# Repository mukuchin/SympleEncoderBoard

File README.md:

SympleEncoderBoard

エンコーダー用基板

神山先輩の回路をEagleで改良したもの

### dipスイッチについて

- 1～6番はエンコーダの回転向きの定義を切り替えるために使う。1～4番はエンコーダの1～4番の向きが切り替わる。5はX,6はY。

- 7は速度を出力するのか、積分したあとの位置を出力するかを切り替える。

- 8は2枚目のボードをつないだときに識別できるようにボード番号を切り替えるためのもの。

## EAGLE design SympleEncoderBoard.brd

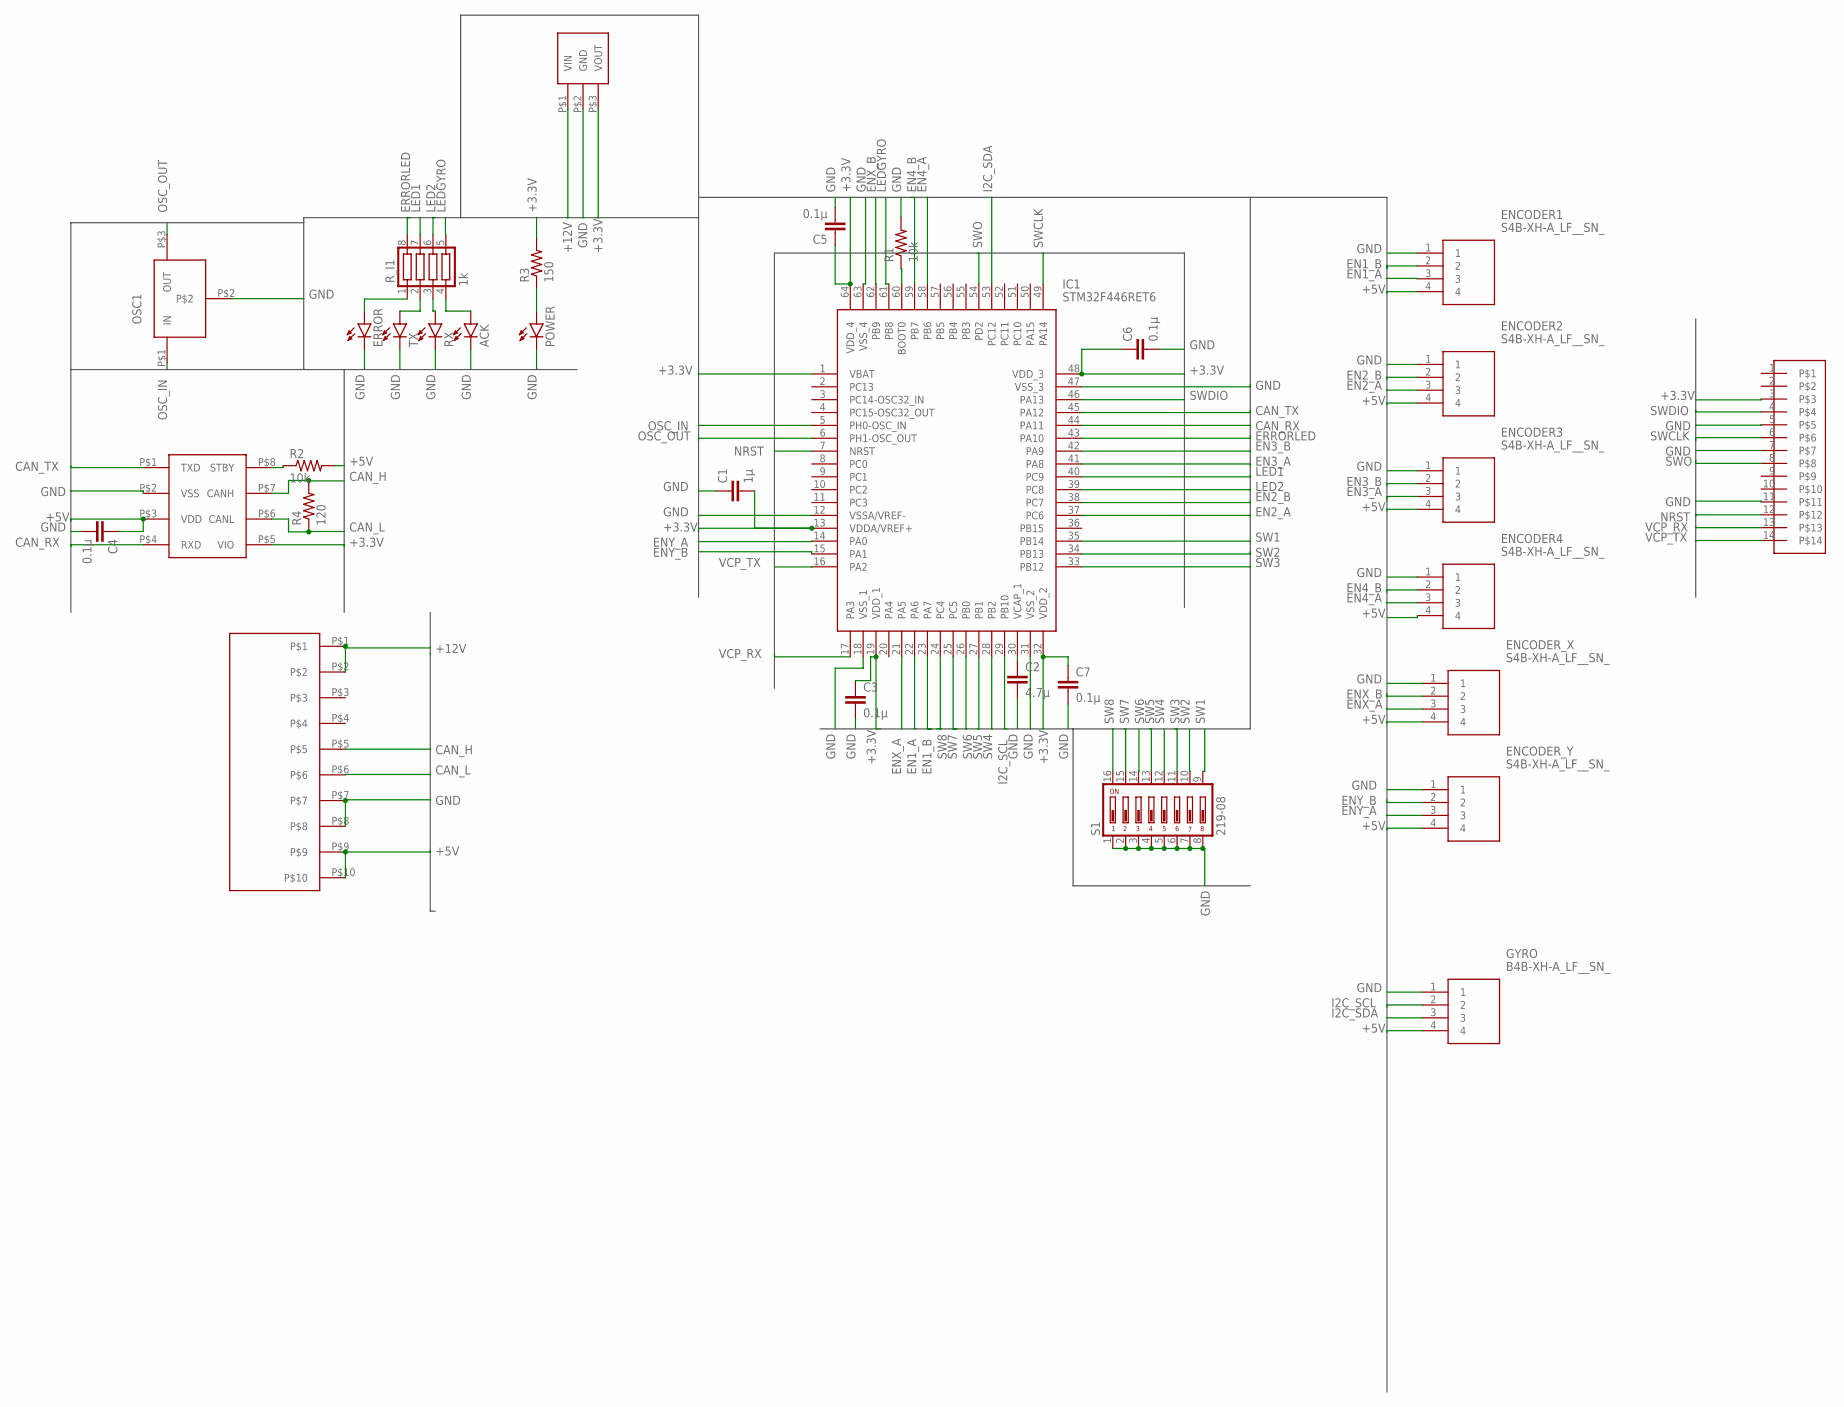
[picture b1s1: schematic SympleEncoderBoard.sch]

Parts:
ACK: LEDCHIPLED_0603; CHIPLED_0603
C1: 1μ; C1608
C2: 4.7μ; C0603
C3, C5, C6, C7: 0.1μ; C0603
C4: 0.1μ; C1608
ENCODER1, ENCODER2, ENCODER3, ENCODER4: S4B-XH-A_LF__SN_; SHDRRA4W64P0X250_1X4_1240X1150
ENCODER_X: S4B-XH-A_LF__SN_; SHDRRA4W64P0X250_1X4_1240X1150
ENCODER_Y: S4B-XH-A_LF__SN_; SHDRRA4W64P0X250_1X4_1240X1150
ERROR: LEDCHIPLED_0603; CHIPLED_0603
GYRO: B4B-XH-A_LF__SN_; SHDR4W64P0X250_1X4_1240X575X70
IC1: STM32F446RET6; QFP50P1200X1200X160-64N
OSC1: CSTN#; CSTNE#
POWER: LEDCHIPLED_0603; CHIPLED_0603
R1, R2: 10k; R0603
R3: 150; R0603
R4: 120; R0603
RX: LEDCHIPLED_0603; CHIPLED_0603
R_I1: 1k; 0603X4RESISTOR
S1: 219-08; CTS-219-08
TX: LEDCHIPLED_0603; CHIPLED_0603
U$1: BOX14P; CON_HEDA14P_1.27
U$2: BP5293-33; DC/DC_REGULATOR_3P
U$3: MCP2562MCP2561-SN; SOIC8
U$4: BOX10PBOX10P-L; BOX10P-L

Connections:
+3.3V: C1.2, C3.1, C5.1, C6.1, C7.1, IC1.1 (VBAT), IC1.13 (VDDA/VREF+), IC1.19 (VDD_1), IC1.32 (VDD_2), IC1.48 (VDD_3), IC1.64 (VDD_4), R3.2, U$1.3, U$2.P$3 (VOUT), U$3.P$5 (VIO)
+5V: C4.1, ENCODER1.4, ENCODER2.4, ENCODER3.4, ENCODER4.4, ENCODER_X.4, ENCODER_Y.4, GYRO.4, R2.2, U$3.P$3 (VDD), U$4.P$9, U$4.P$10
+12V: U$2.P$1 (VIN), U$4.P$1, U$4.P$2
CAN_H: R4.2, U$3.P$7 (CANH), U$4.P$5
CAN_L: R4.1, U$3.P$6 (CANL), U$4.P$6
CAN_RX: IC1.44 (PA11), U$3.P$4 (RXD)
CAN_TX: IC1.45 (PA12), U$3.P$1 (TXD)
EN1_A: ENCODER1.3, IC1.22 (PA6)
EN1_B: ENCODER1.2, IC1.23 (PA7)
EN2_A: ENCODER2.3, IC1.37 (PC6)
EN2_B: ENCODER2.2, IC1.38 (PC7)
EN3_A: ENCODER3.3, IC1.41 (PA8)
EN3_B: ENCODER3.2, IC1.42 (PA9)
EN4_A: ENCODER4.3, IC1.58 (PB6)
EN4_B: ENCODER4.2, IC1.59 (PB7)
ENX_A: ENCODER_X.3, IC1.21 (PA5)
ENX_B: ENCODER_X.2, IC1.62 (PB9)
ENY_A: ENCODER_Y.3, IC1.14 (PA0)
ENY_B: ENCODER_Y.2, IC1.15 (PA1)
ERRORLED: IC1.43 (PA10), R_I1.8
GND: ACK.C, C1.1, C2.2, C3.2, C4.2, C5.2, C6.2, C7.2, ENCODER1.1, ENCODER2.1, ENCODER3.1, ENCODER4.1, ENCODER_X.1, ENCODER_Y.1, ERROR.C, GYRO.1, IC1.12 (VSSA/VREF-), IC1.18 (VSS_1), IC1.31 (VSS_2), IC1.47 (VSS_3), IC1.63 (VSS_4), OSC1.P$2, POWER.C, R1.2, RX.C, S1.1, S1.2, S1.3, S1.4, S1.5, S1.6, S1.7, S1.8, TX.C, U$1.5, U$1.7, U$1.11, U$2.P$2 (GND), U$3.P$2 (VSS), U$4.P$7, U$4.P$8
I2C_SCL: GYRO.2, IC1.29 (PB10)
I2C_SDA: GYRO.3, IC1.53 (PC12)
LED1: IC1.40 (PC9), R_I1.7
LED2: IC1.39 (PC8), R_I1.6
LEDGYRO: IC1.61 (PB8), R_I1.5
unnamed: IC1.60 (BOOT0), R1.1
unnamed: C2.1, IC1.30 (VCAP_1)
unnamed: ERROR.A, R_I1.1
unnamed: R_I1.2, TX.A
unnamed: RX.A, R_I1.3
unnamed: ACK.A, R_I1.4
unnamed: R2.1, U$3.P$8 (STBY)
unnamed: POWER.A, R3.1
NRST: IC1.7 (NRST), U$1.12
OSC_IN: IC1.5 (PH0-OSC_IN), OSC1.P$1 (IN)
OSC_OUT: IC1.6 (PH1-OSC_OUT), OSC1.P$3 (OUT)
SW1: IC1.35 (PB14), S1.9
SW2: IC1.34 (PB13), S1.10
SW3: IC1.33 (PB12), S1.11
SW4: IC1.28 (PB2), S1.12
SW5: IC1.27 (PB1), S1.13
SW6: IC1.26 (PB0), S1.14
SW7: IC1.25 (PC5), S1.15
SW8: IC1.24 (PC4), S1.16
SWCLK: IC1.49 (PA14), U$1.6
SWDIO: IC1.46 (PA13), U$1.4
SWO: IC1.54 (PD2), U$1.8
VCP_RX: IC1.17 (PA3), U$1.13
VCP_TX: IC1.16 (PA2), U$1.14

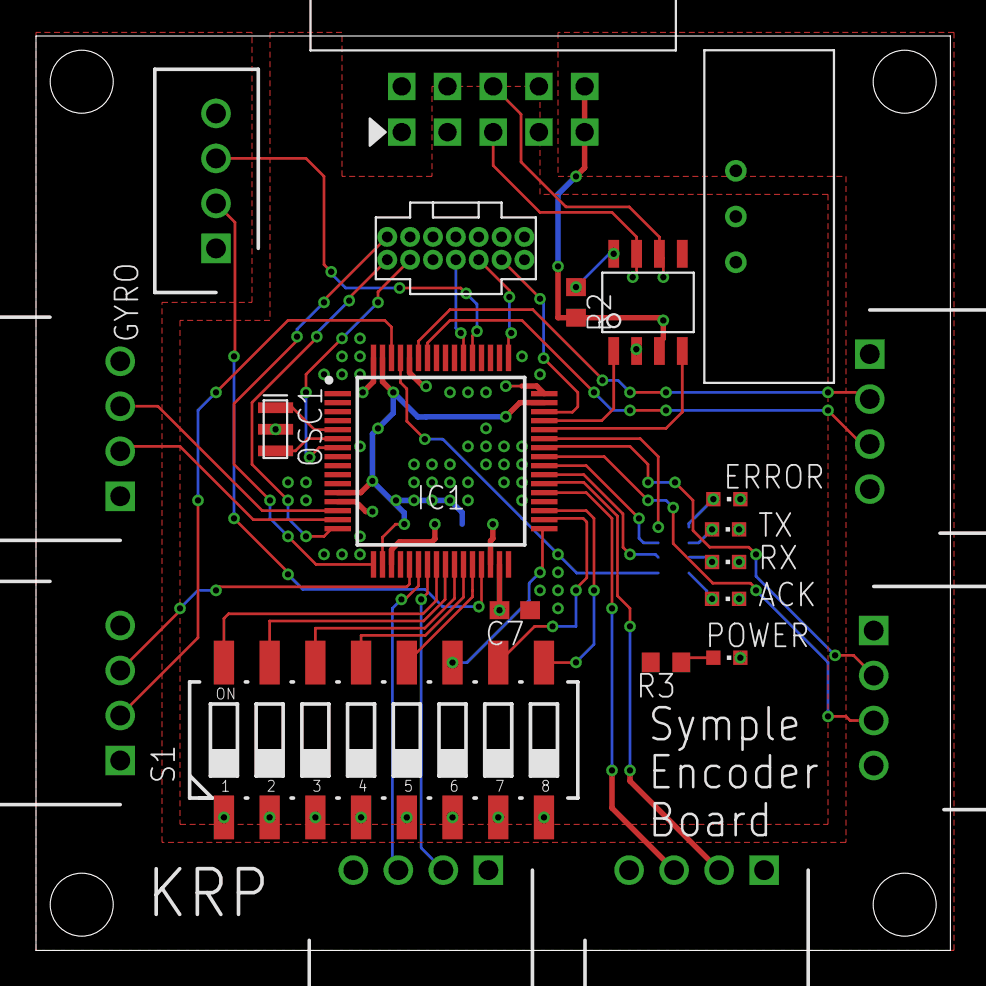
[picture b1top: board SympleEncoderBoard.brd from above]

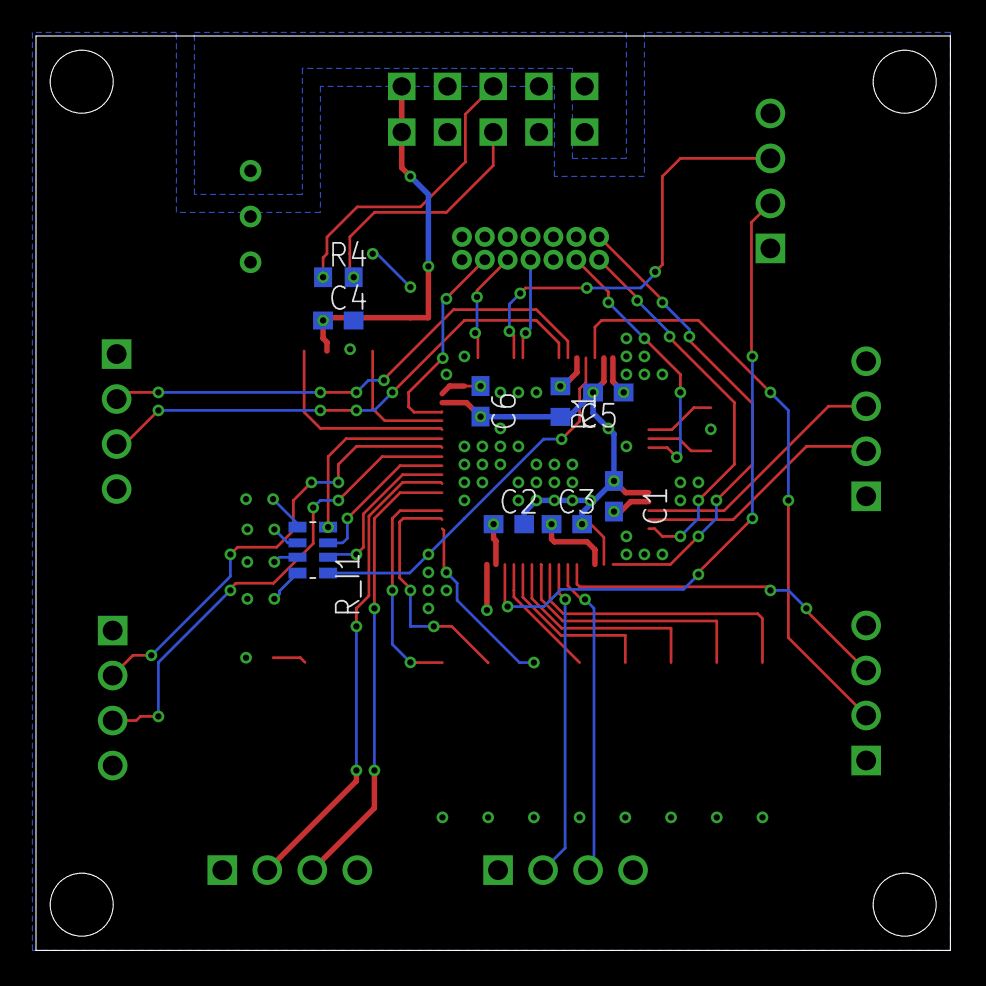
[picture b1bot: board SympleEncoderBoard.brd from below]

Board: 2 copper layers, 50.8 x 50.8 mm, 31 parts (9 on the bottom side), 50 nets.

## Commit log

2020-10-20 .sch加えた
2020-10-20 無駄なもの消した
2020-10-20 コミットしたよ
2020-10-22 README.mdを加えたよ
2020-10-22 .schと.brd作ったよ
2020-10-22 ライブラリとかバスを作った
2020-10-22 ライブラリとかバスを作っただけ
2020-10-28 回路図は完成、コネクタつけた
2020-11-01 回路図書きました
2020-11-01 10pboxのピンアサイン間違えてました
2020-11-02 CANトランシーバの位置と型番更新、MLCC・VDD・VSS接続、配線太さ、14Pコネクタ配置変更
2020-11-02 GYRO用XHコネクタを横から縦に、テキストの文字を少し拡大、ベタパターンDRCチェック済
2020-11-02 GRYO用コネクタを横から縦に、テキストの文字を少し拡大、ベタパターンDRCチェック済、ガーバーデータ追加
2020-11-10 配線を何箇所か短くした
2020-11-11 基板の部品位置の変更
2020-11-24 回路図のエラーを直した。部品リストを作成した。
2020-11-27 エラー等修正しました。
2020-11-27 コネクタのホール修正しました
2020-11-27 集合抵抗の値を変えました
2020-12-02 SDAピンをPC11からPC12に修正した。
2021-01-08 サーマルビアによる導通のエラーを直した
2021-03-27 テキストファイルで部品表を作った
